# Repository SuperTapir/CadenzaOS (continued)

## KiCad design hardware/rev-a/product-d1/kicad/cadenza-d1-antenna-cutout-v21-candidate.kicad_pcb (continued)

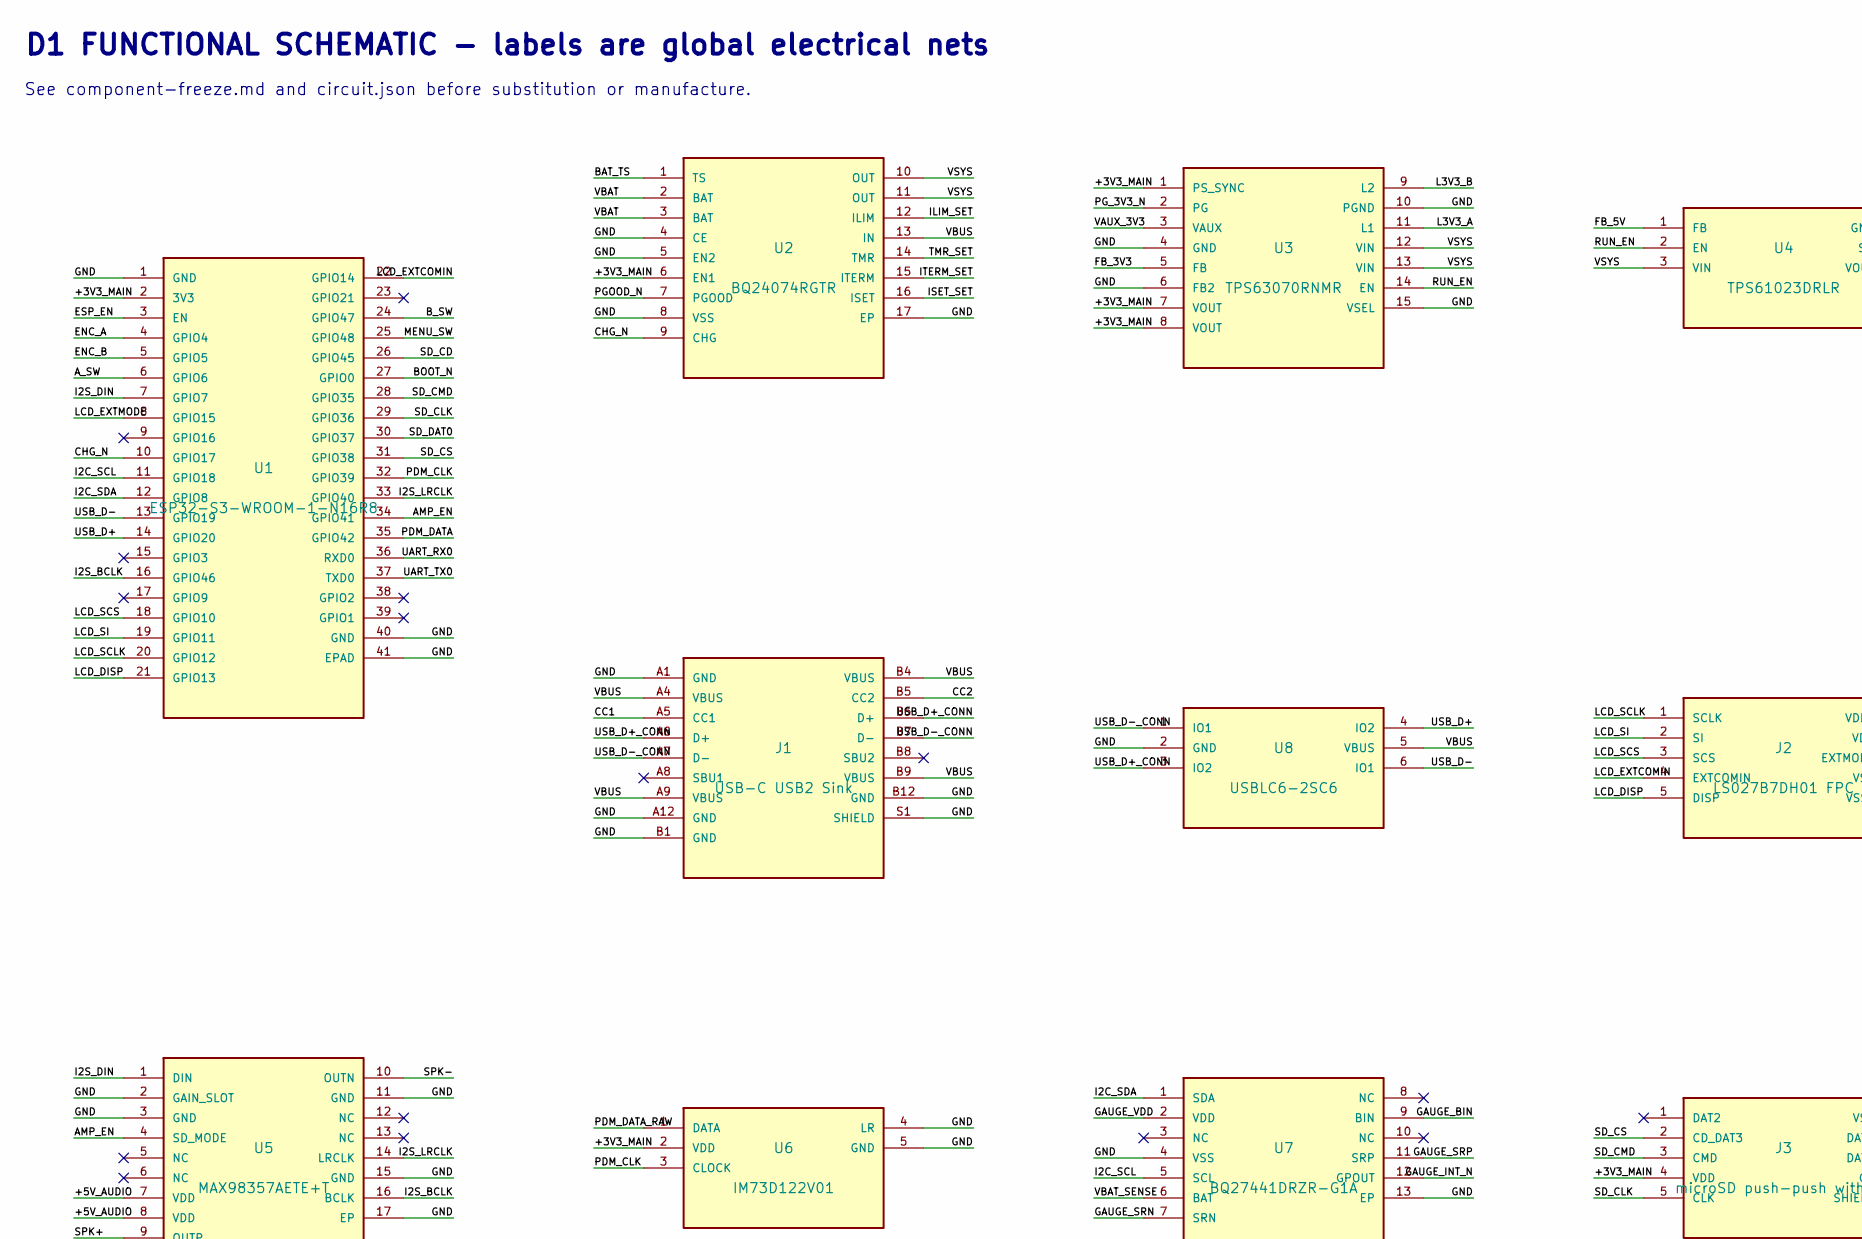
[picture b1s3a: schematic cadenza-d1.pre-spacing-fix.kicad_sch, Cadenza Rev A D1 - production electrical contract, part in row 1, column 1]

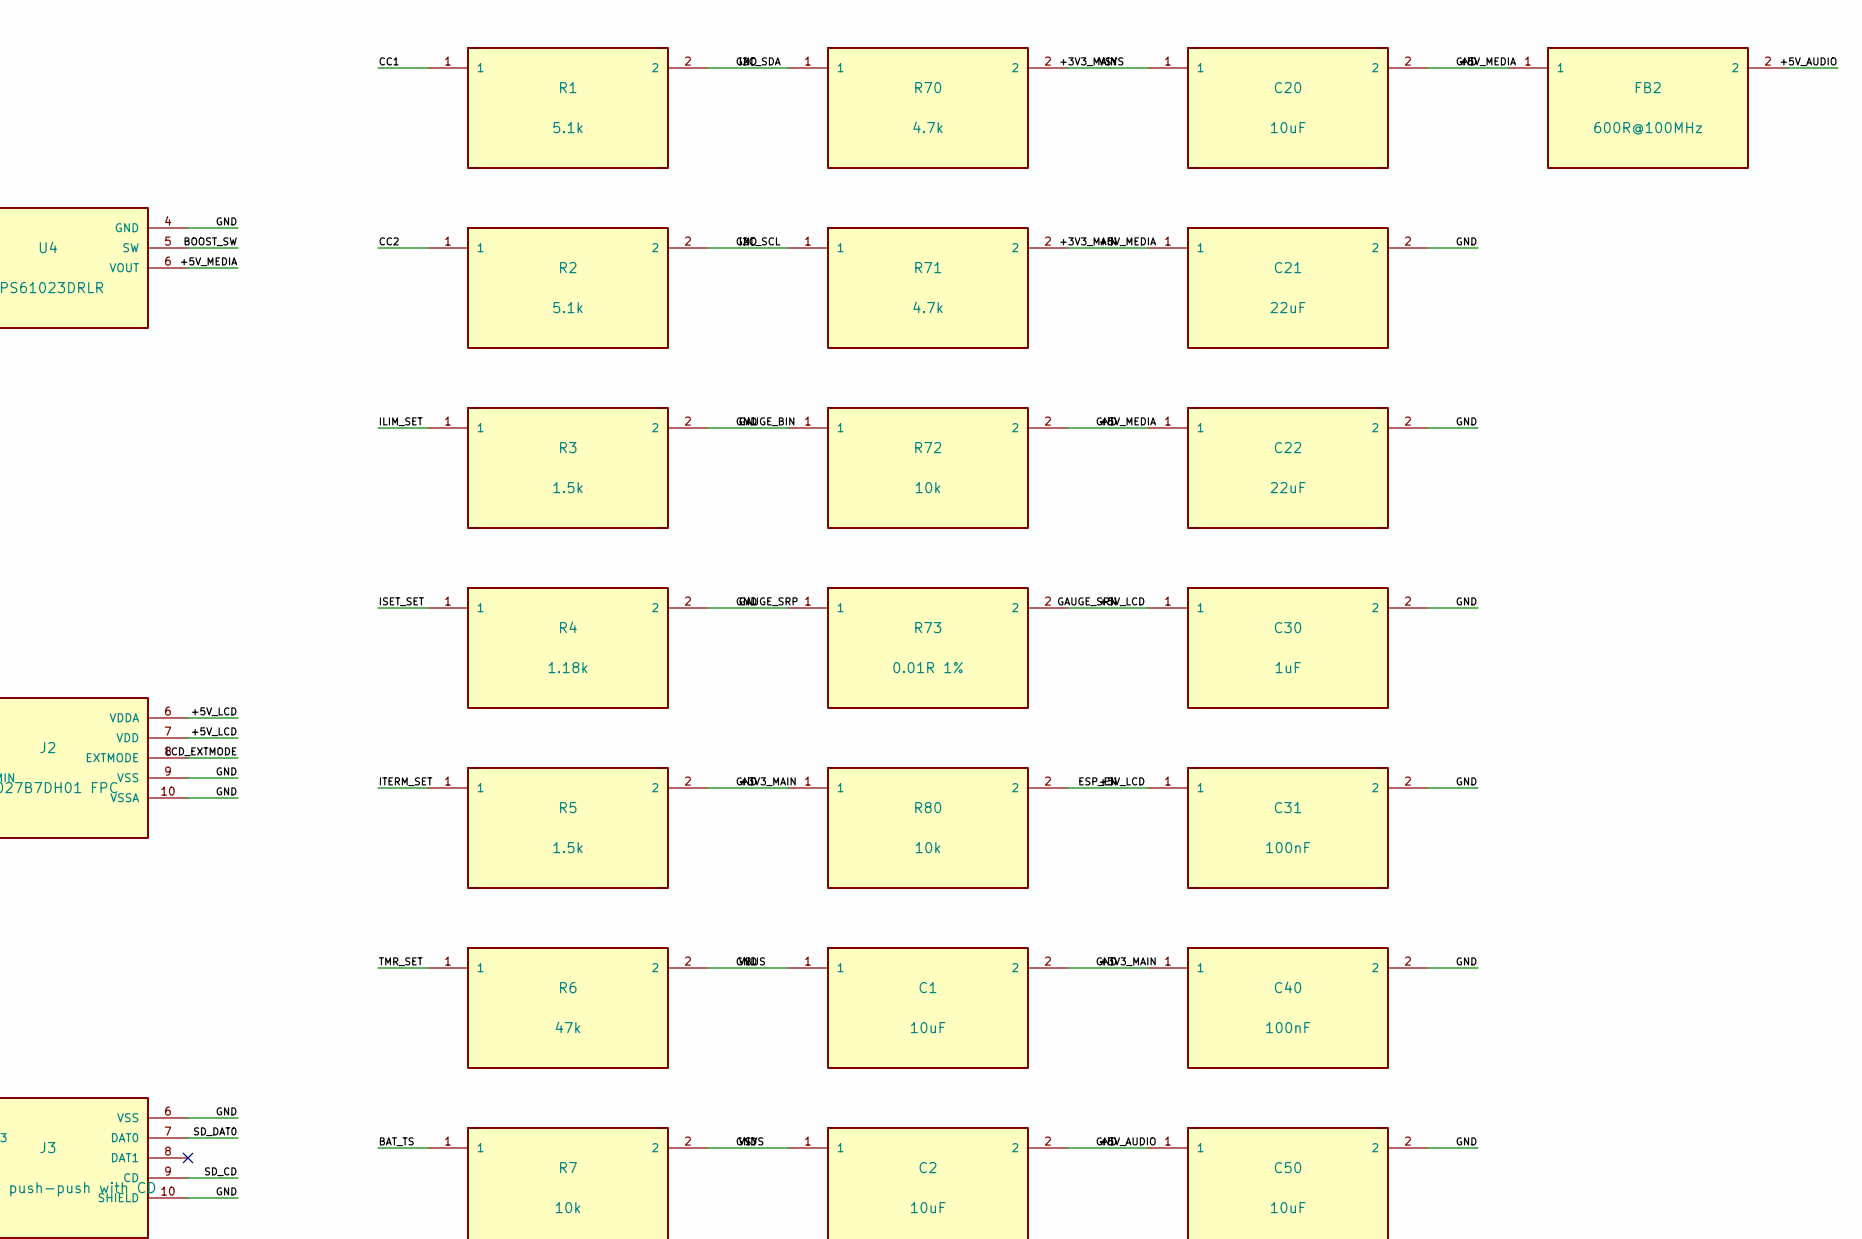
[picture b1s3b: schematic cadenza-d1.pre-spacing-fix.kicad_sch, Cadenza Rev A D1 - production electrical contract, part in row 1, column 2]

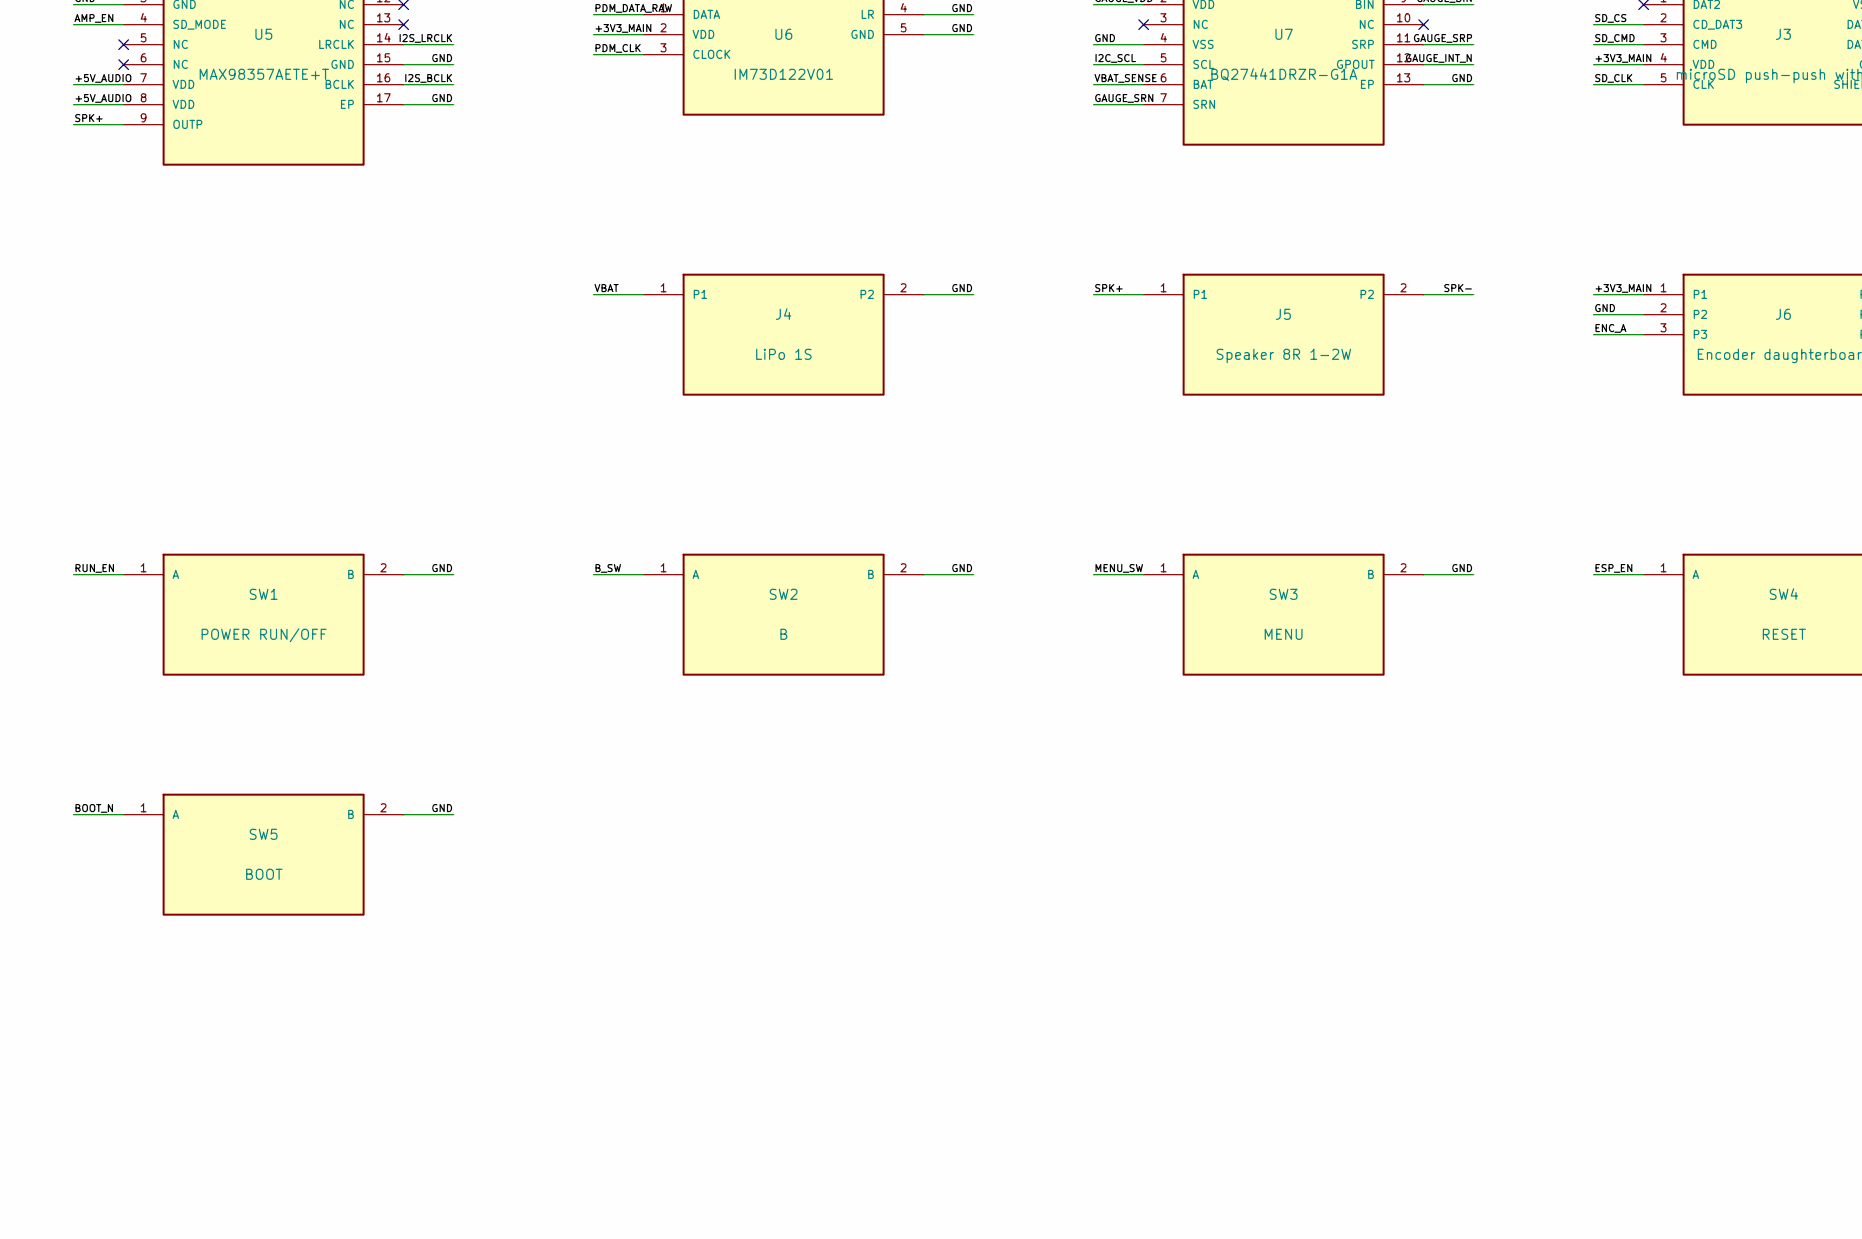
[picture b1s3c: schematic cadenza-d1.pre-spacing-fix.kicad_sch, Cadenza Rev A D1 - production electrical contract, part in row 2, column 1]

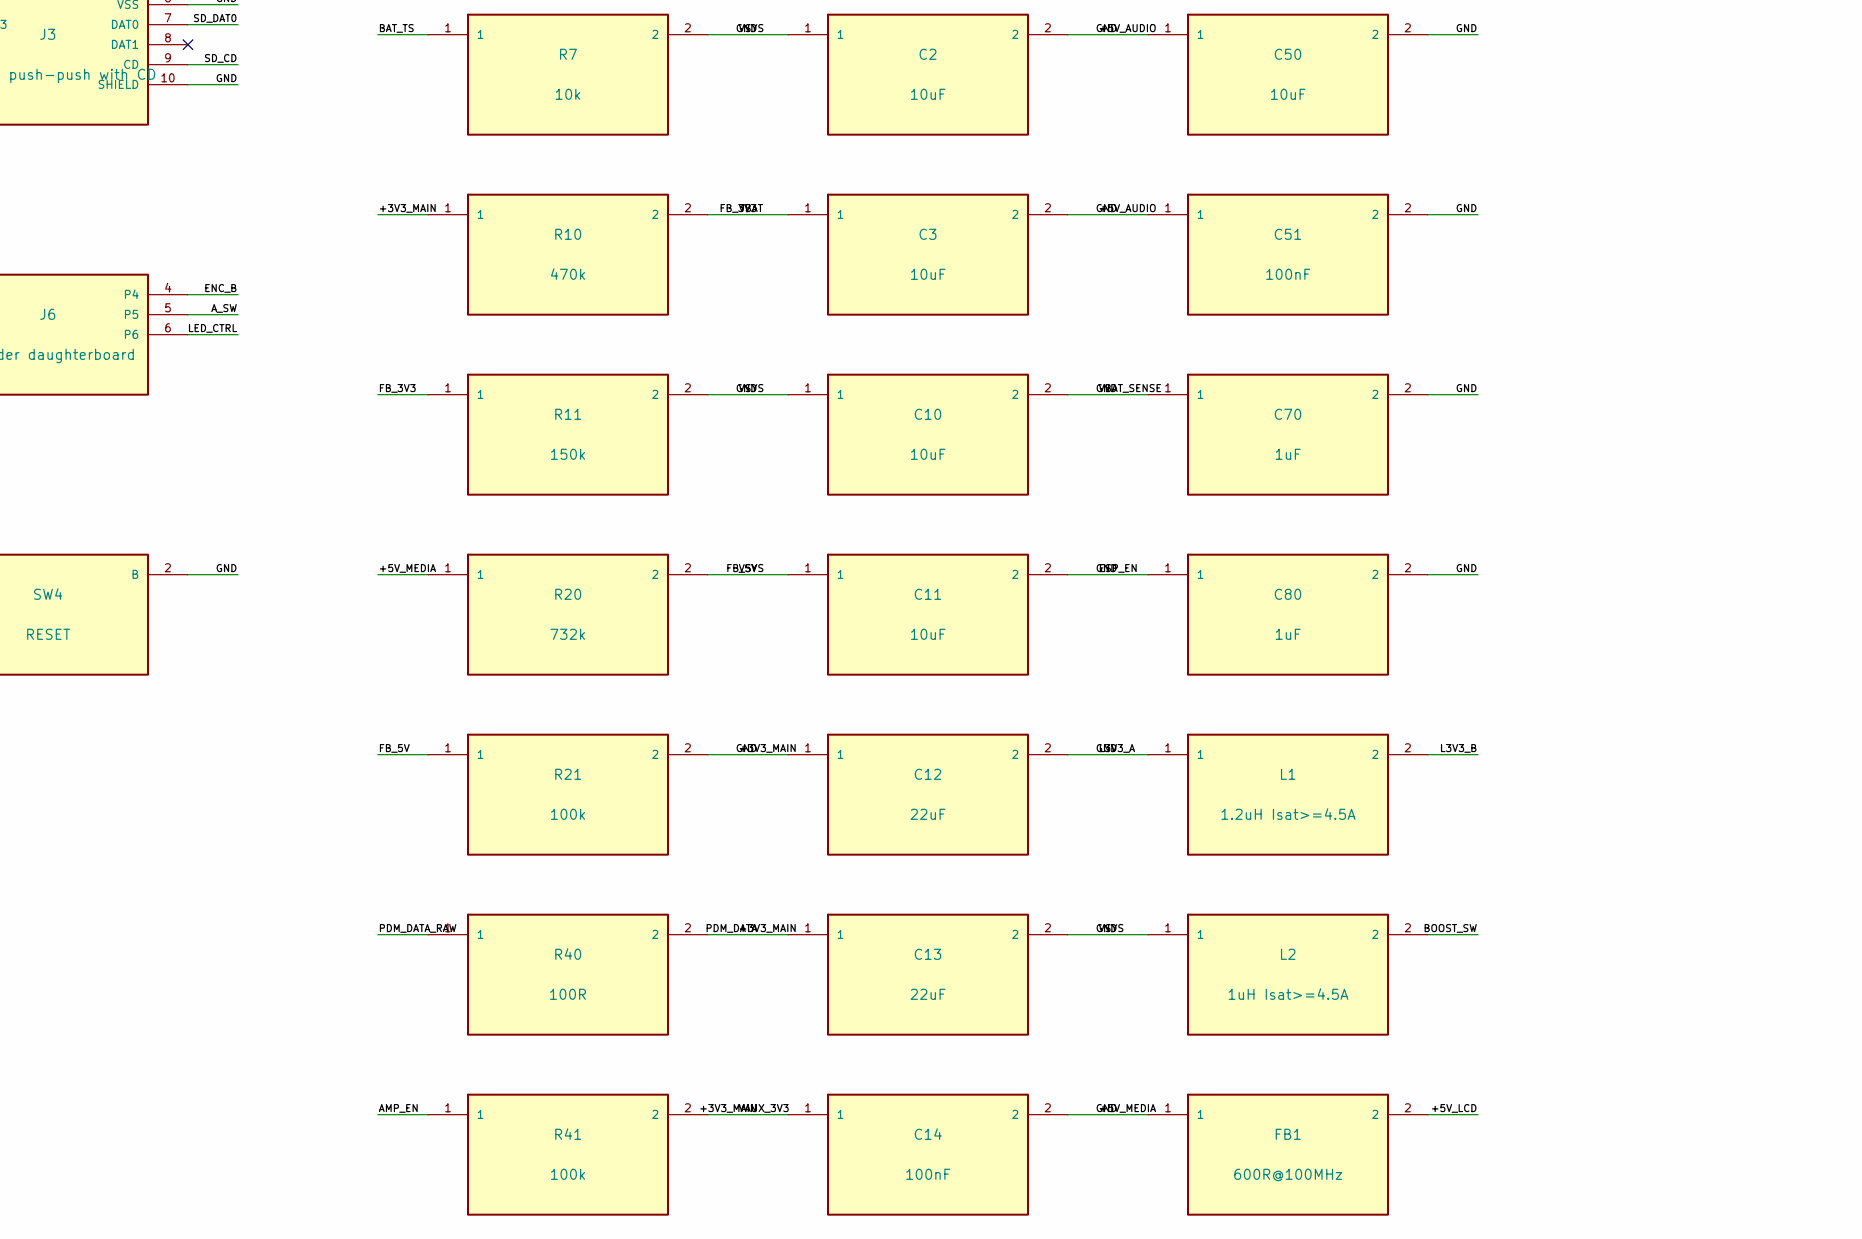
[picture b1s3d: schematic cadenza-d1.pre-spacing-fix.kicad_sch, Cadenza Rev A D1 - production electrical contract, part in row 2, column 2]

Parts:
C1, C2, C3, C10, C11, C20, C50: 10uF; C_0603_1608Metric
C12, C13, C21, C22: 22uF; C_0603_1608Metric
C14, C31, C40, C51: 100nF; C_0603_1608Metric
C30, C70, C80: 1uF; C_0603_1608Metric
FB1, FB2: 600R@100MHz; L_0603_1608Metric
J1: USB-C USB2 Sink; USB_C_Receptacle_HCTL_HC-TYPE-C-16P-01A
J2: LS027B7DH01 FPC; Hirose_FH34SRJ-10S-0.5SH
J3: microSD push-push with CD; MICROSD_SAMPLE_GATE
J4: LiPo 1S; JST_PH_B2B-PH-SM4-TB_1x02-1MP_P2.00mm_Vertical
J5: Speaker 8R 1-2W; JST_PH_B2B-PH-SM4-TB_1x02-1MP_P2.00mm_Vertical
J6: Encoder daughterboard; JST_SH_SM06B-SRSS-TB_1x06-1MP_P1.00mm_Horizontal
L1: 1.2uH Isat>=4.5A; L_1210_3225Metric
L2: 1uH Isat>=4.5A; L_1210_3225Metric
R1, R2: 5.1k; R_0603_1608Metric
R3, R5: 1.5k; R_0603_1608Metric
R4: 1.18k; R_0603_1608Metric
R6: 47k; R_0603_1608Metric
R7, R72, R80: 10k; R_0603_1608Metric
R10: 470k; R_0603_1608Metric
R11: 150k; R_0603_1608Metric
R20: 732k; R_0603_1608Metric
R21, R41: 100k; R_0603_1608Metric
R40: 100R; R_0603_1608Metric
R70, R71: 4.7k; R_0603_1608Metric
R73: 0.01R 1%; R_0603_1608Metric
SW1: POWER RUN/OFF; SW_SPDT_CK_JS102011SAQN
SW2: B; SW_Push_1P1T_NO_CK_KMR2
SW3: MENU; SW_Push_1P1T_NO_CK_KMR2
SW4: RESET; SW_Push_1P1T_NO_CK_KMR2
SW5: BOOT; SW_Push_1P1T_NO_CK_KMR2
U1: ESP32-S3-WROOM-1-N16R8; ESP32-S3-WROOM-1
U2: BQ24074RGTR; VQFN-16-1EP_3x3mm_P0.5mm_EP1.68x1.68mm_ThermalVias
U3: TPS63070RNMR; TI_RNM0015A_VQFN-HR-15_2.5x3mm
U4: TPS61023DRLR; TI_DRL0006A_SOT-563
U5: MAX98357AETE+T; TQFN-16-1EP_3x3mm_P0.5mm_EP1.23x1.23mm_ThermalVias
U6: IM73D122V01; Infineon_IM73D122V01_PG-LLGA-5-3
U7: BQ27441DRZR-G1A; TI_DRZ0012A_VSON-12_2.5x4mm
U8: USBLC6-2SC6; SOT-23-6

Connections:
/AMP_EN: R41.1, U1.34 (GPIO41), U5.4 (SD_MODE)
/A_SW: J6.5, U1.6 (GPIO6)
/BAT_TS: R7.1, U2.1 (TS)
/BOOST_SW: L2.2, U4.5 (SW)
/BOOT_N: SW5.1 (A), U1.27 (GPIO0)
/B_SW: SW2.1 (A), U1.24 (GPIO47)
/CC1: J1.A5 (CC1), R1.1
/CC2: J1.B5 (CC2), R2.1
/CHG_N: U1.10 (GPIO17), U2.9 (CHG)
/ENC_A: J6.3, U1.4 (GPIO4)
/ENC_B: J6.4, U1.5 (GPIO5)
/GAUGE_INT_N: U7.12 (GPOUT)
/GAUGE_VDD: U7.2 (VDD)
/I2S_BCLK: U1.16 (GPIO46), U5.16 (BCLK)
/I2S_DIN: U1.7 (GPIO7), U5.1 (DIN)
/I2S_LRCLK: U1.33 (GPIO40), U5.14 (LRCLK)
/ILIM_SET: R3.1, U2.12 (ILIM)
/ISET_SET: R4.1, U2.16 (ISET)
/ITERM_SET: R5.1, U2.15 (ITERM)
/L3V3_B: L1.2, U3.9 (L2)
/LCD_DISP: J2.5 (DISP), U1.21 (GPIO13)
/LCD_EXTCOMIN: J2.4 (EXTCOMIN), U1.22 (GPIO14)
/LCD_EXTMODE: J2.8 (EXTMODE), U1.8 (GPIO15)
/LCD_SCLK: J2.1 (SCLK), U1.20 (GPIO12)
/LCD_SCS: J2.3 (SCS), U1.18 (GPIO10)
/LCD_SI: J2.2 (SI), U1.19 (GPIO11)
/LED_CTRL: J6.6
/MENU_SW: SW3.1 (A), U1.25 (GPIO48)
/PDM_CLK: U1.32 (GPIO39), U6.3 (CLOCK)
/PDM_DATA_RAW: R40.1, U6.1 (DATA)
/PGOOD_N: U2.7 (PGOOD)
/PG_3V3_N: U3.2 (PG)
/RUN_EN: SW1.1 (A), U3.14 (EN), U4.2 (EN)
/SD_CD: J3.9 (CD), U1.26 (GPIO45)
/SD_CLK: J3.5 (CLK), U1.29 (GPIO36)
/SD_CMD: J3.3 (CMD), U1.28 (GPIO35)
/SD_CS: J3.2 (CD_DAT3), U1.31 (GPIO38)
/SD_DAT0: J3.7 (DAT0), U1.30 (GPIO37)
/SPK+: J5.1, U5.9 (OUTP)
/SPK-: J5.2, U5.10 (OUTN)
/TMR_SET: R6.1, U2.14 (TMR)
/UART_RX0: U1.36 (RXD0)
/UART_TX0: U1.37 (TXD0)
/USB_D+: U1.14 (GPIO20), U8.4 (IO2)
/USB_D+_CONN: J1.A6 (D+), J1.B6 (D+), U8.3 (IO2)
/USB_D-: U1.13 (GPIO19), U8.6 (IO1)
/USB_D-_CONN: J1.A7 (D-), J1.B7 (D-), U8.1 (IO1)

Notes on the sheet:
D1 FUNCTIONAL SCHEMATIC - labels are global electrical nets
See component-freeze.md and circuit.json before substitution or manufacture.

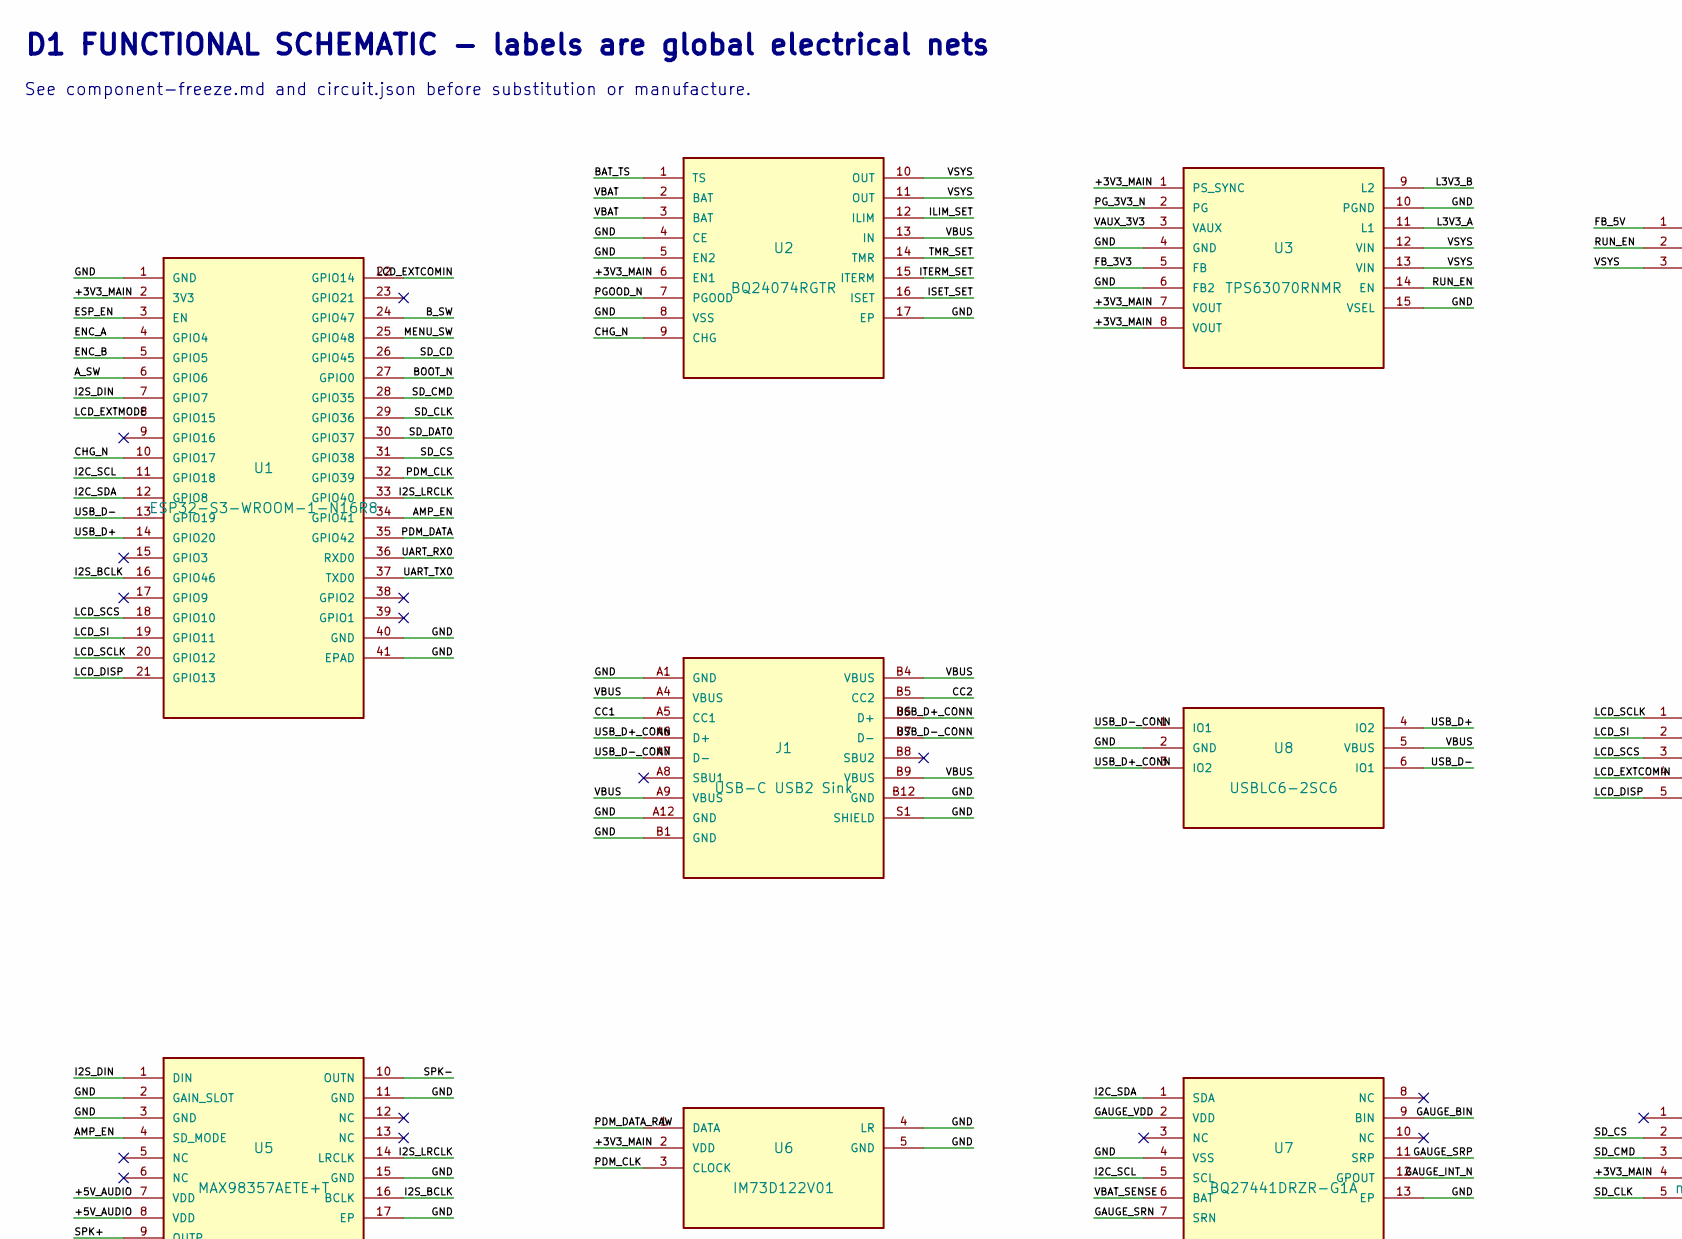
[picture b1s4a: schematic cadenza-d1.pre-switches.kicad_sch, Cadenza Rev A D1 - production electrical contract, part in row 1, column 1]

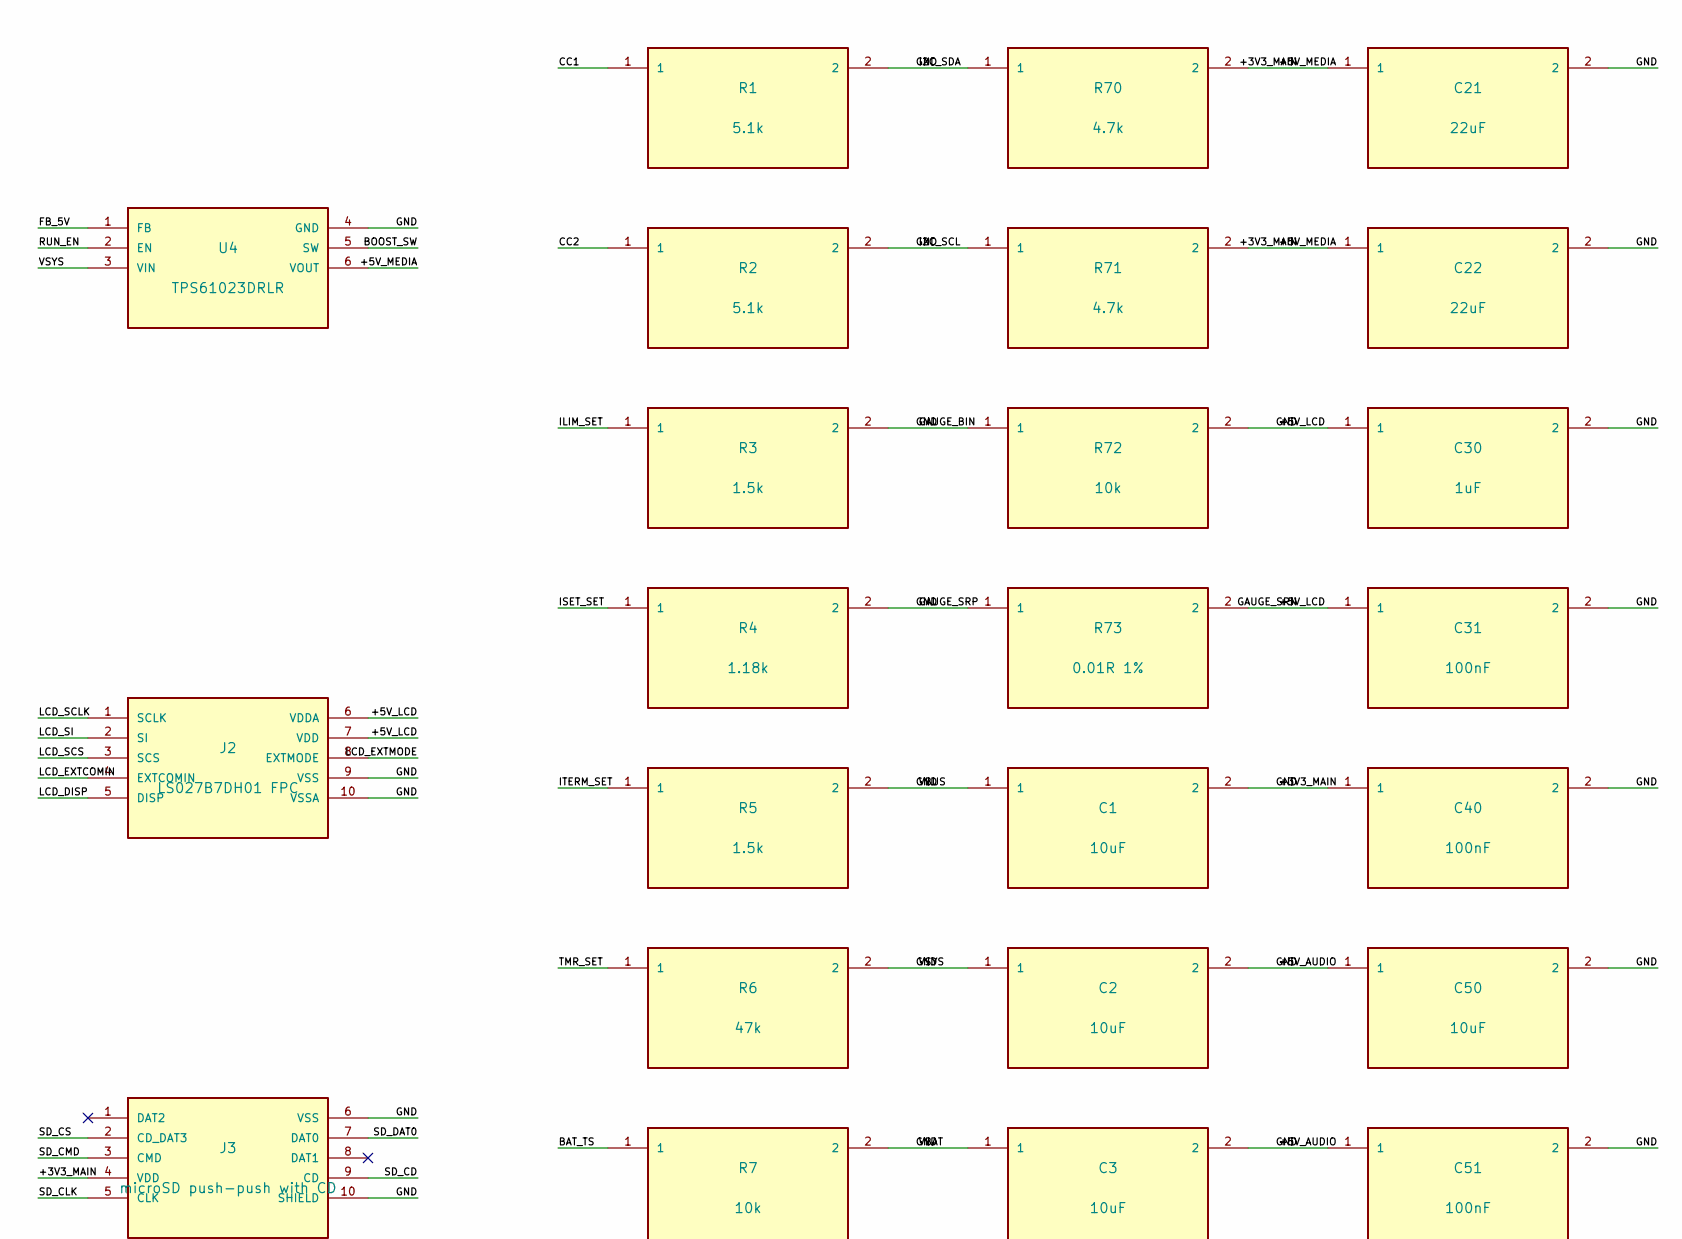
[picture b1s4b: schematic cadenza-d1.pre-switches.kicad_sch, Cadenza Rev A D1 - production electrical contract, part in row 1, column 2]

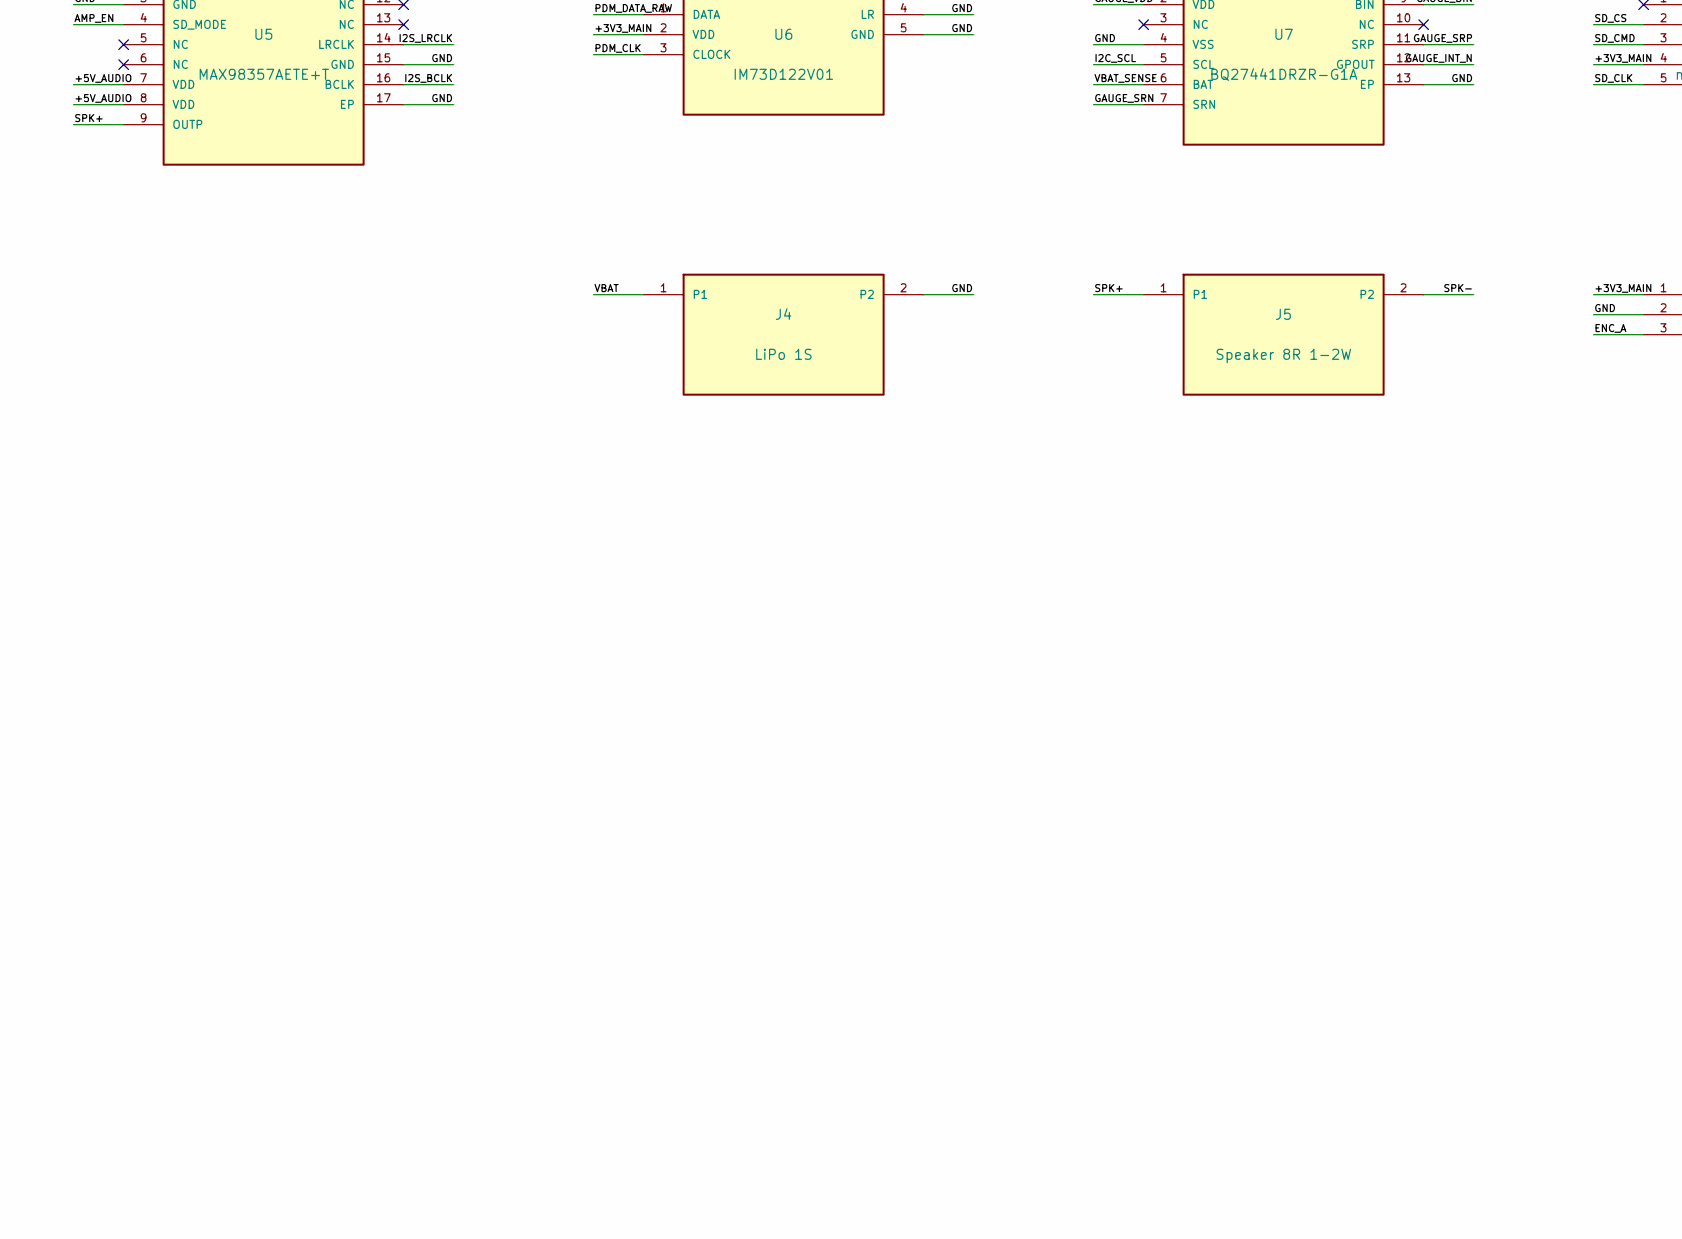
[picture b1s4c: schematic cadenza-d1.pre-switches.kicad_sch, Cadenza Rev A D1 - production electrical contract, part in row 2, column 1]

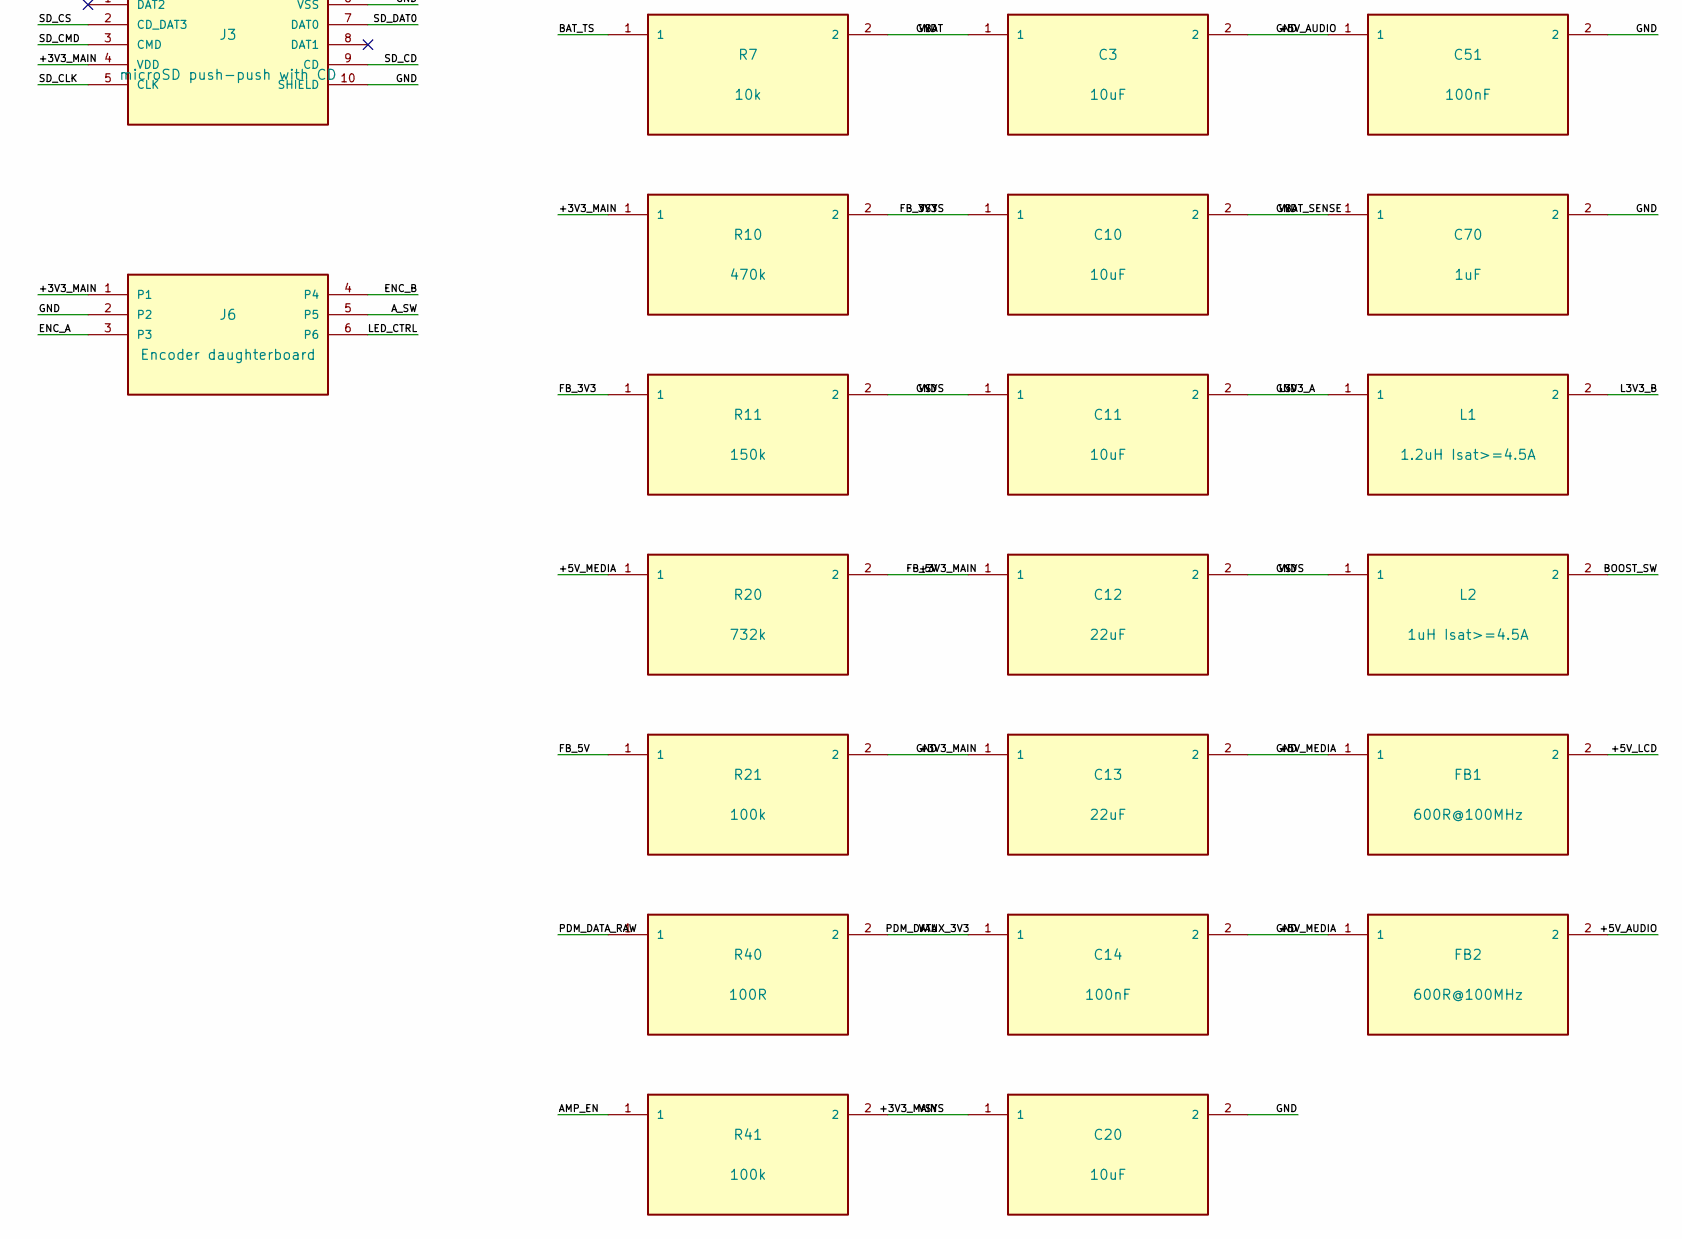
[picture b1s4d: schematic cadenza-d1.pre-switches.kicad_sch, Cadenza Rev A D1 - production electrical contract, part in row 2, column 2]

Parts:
C1, C2, C3, C10, C11, C20, C50: 10uF; C_0603_1608Metric
C12, C13, C21, C22: 22uF; C_0603_1608Metric
C14, C31, C40, C51: 100nF; C_0603_1608Metric
C30, C70: 1uF; C_0603_1608Metric
FB1, FB2: 600R@100MHz; L_0603_1608Metric
J1: USB-C USB2 Sink; USB_C_Receptacle_HCTL_HC-TYPE-C-16P-01A
J2: LS027B7DH01 FPC; Hirose_FH34SRJ-10S-0.5SH
J3: microSD push-push with CD; MICROSD_SAMPLE_GATE
J4: LiPo 1S; JST_PH_B2B-PH-SM4-TB_1x02-1MP_P2.00mm_Vertical
J5: Speaker 8R 1-2W; JST_PH_B2B-PH-SM4-TB_1x02-1MP_P2.00mm_Vertical
J6: Encoder daughterboard; JST_SH_SM06B-SRSS-TB_1x06-1MP_P1.00mm_Horizontal
L1: 1.2uH Isat>=4.5A; L_2520_1008Metric
L2: 1uH Isat>=4.5A; L_2520_1008Metric
R1, R2: 5.1k; R_0603_1608Metric
R3, R5: 1.5k; R_0603_1608Metric
R4: 1.18k; R_0603_1608Metric
R6: 47k; R_0603_1608Metric
R7, R72: 10k; R_0603_1608Metric
R10: 470k; R_0603_1608Metric
R11: 150k; R_0603_1608Metric
R20: 732k; R_0603_1608Metric
R21, R41: 100k; R_0603_1608Metric
R40: 100R; R_0603_1608Metric
R70, R71: 4.7k; R_0603_1608Metric
R73: 0.01R 1%; R_0603_1608Metric
U1: ESP32-S3-WROOM-1-N16R8; ESP32-S3-WROOM-1
U2: BQ24074RGTR; VQFN-16-1EP_3x3mm_P0.5mm_EP1.68x1.68mm_ThermalVias
U3: TPS63070RNMR; TI_RNM0015A_VQFN-HR-15_2.5x3mm
U4: TPS61023DRLR; TI_DRL0006A_SOT-563
U5: MAX98357AETE+T; TQFN-16-1EP_3x3mm_P0.5mm_EP1.23x1.23mm_ThermalVias
U6: IM73D122V01; Infineon_IM73D122V01_PG-LLGA-5-3
U7: BQ27441DRZR-G1A; TI_DRZ0012A_VSON-12_2.5x4mm
U8: USBLC6-2SC6; SOT-23-6

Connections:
/AMP_EN: R41.1, U1.34 (GPIO41), U5.4 (SD_MODE)
/A_SW: J6.5, U1.6 (GPIO6)
/BAT_TS: R7.1, U2.1 (TS)
/BOOST_SW: L2.2, U4.5 (SW)
/BOOT_N: U1.27 (GPIO0); also elsewhere on the board
/B_SW: U1.24 (GPIO47); also elsewhere on the board
/CC1: J1.A5 (CC1), R1.1
/CC2: J1.B5 (CC2), R2.1
/CHG_N: U1.10 (GPIO17), U2.9 (CHG)
/ENC_A: J6.3, U1.4 (GPIO4)
/ENC_B: J6.4, U1.5 (GPIO5)
/GAUGE_INT_N: U7.12 (GPOUT)
/GAUGE_VDD: U7.2 (VDD)
/I2S_BCLK: U1.16 (GPIO46), U5.16 (BCLK)
/I2S_DIN: U1.7 (GPIO7), U5.1 (DIN)
/I2S_LRCLK: U1.33 (GPIO40), U5.14 (LRCLK)
/ILIM_SET: R3.1, U2.12 (ILIM)
/ISET_SET: R4.1, U2.16 (ISET)
/ITERM_SET: R5.1, U2.15 (ITERM)
/L3V3_B: L1.2, U3.9 (L2)
/LCD_DISP: J2.5 (DISP), U1.21 (GPIO13)
/LCD_EXTCOMIN: J2.4 (EXTCOMIN), U1.22 (GPIO14)
/LCD_EXTMODE: J2.8 (EXTMODE), U1.8 (GPIO15)
/LCD_SCLK: J2.1 (SCLK), U1.20 (GPIO12)
/LCD_SCS: J2.3 (SCS), U1.18 (GPIO10)
/LCD_SI: J2.2 (SI), U1.19 (GPIO11)
/LED_CTRL: J6.6
/MENU_SW: U1.25 (GPIO48); also elsewhere on the board
/PDM_CLK: U1.32 (GPIO39), U6.3 (CLOCK)
/PDM_DATA_RAW: R40.1, U6.1 (DATA)
/PGOOD_N: U2.7 (PGOOD)
/PG_3V3_N: U3.2 (PG)
/RUN_EN: U3.14 (EN), U4.2 (EN); also elsewhere on the board
/SD_CD: J3.9 (CD), U1.26 (GPIO45)
/SD_CLK: J3.5 (CLK), U1.29 (GPIO36)
/SD_CMD: J3.3 (CMD), U1.28 (GPIO35)
/SD_CS: J3.2 (CD_DAT3), U1.31 (GPIO38)
/SD_DAT0: J3.7 (DAT0), U1.30 (GPIO37)
/SPK+: J5.1, U5.9 (OUTP)
/SPK-: J5.2, U5.10 (OUTN)
/TMR_SET: R6.1, U2.14 (TMR)
/UART_RX0: U1.36 (RXD0)
/UART_TX0: U1.37 (TXD0)
/USB_D+: U1.14 (GPIO20), U8.4 (IO2)
/USB_D+_CONN: J1.A6 (D+), J1.B6 (D+), U8.3 (IO2)
/USB_D-: U1.13 (GPIO19), U8.6 (IO1)
/USB_D-_CONN: J1.A7 (D-), J1.B7 (D-), U8.1 (IO1)

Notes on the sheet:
D1 FUNCTIONAL SCHEMATIC - labels are global electrical nets
See component-freeze.md and circuit.json before substitution or manufacture.

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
